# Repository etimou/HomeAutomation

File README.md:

# HomeAutomation

Installation on Raspberrypi
---------------------------

1. git clone https://github.com/etimou/HomeAutomation
2. sudo apt-get install python-serial lighttpd
3. sudo cp /etc/lighttpd/lighttpd.conf /etc/lighttpd/lighttpd.conf.sav
4. sudo nano /etc/lighttpd/lighttpd.conf
   replace "/var/www/html" by "/home/pi/HomeAutomation/software/raspberrypi/www"
   add "mod_cgi" in the server.modules section

   add
   cgi.assign                 = ( ".pl"  => "/usr/bin/perl",
                               ".cgi" => "/usr/bin/perl",
                               ".rb"  => "/usr/bin/ruby",
                               ".erb" => "/usr/bin/eruby",
                               ".py"  => "/usr/bin/python",
                               ".php" => "/usr/bin/php-cgi" )
  change port from 80 to 8181

5. sudo service lighttpd restart

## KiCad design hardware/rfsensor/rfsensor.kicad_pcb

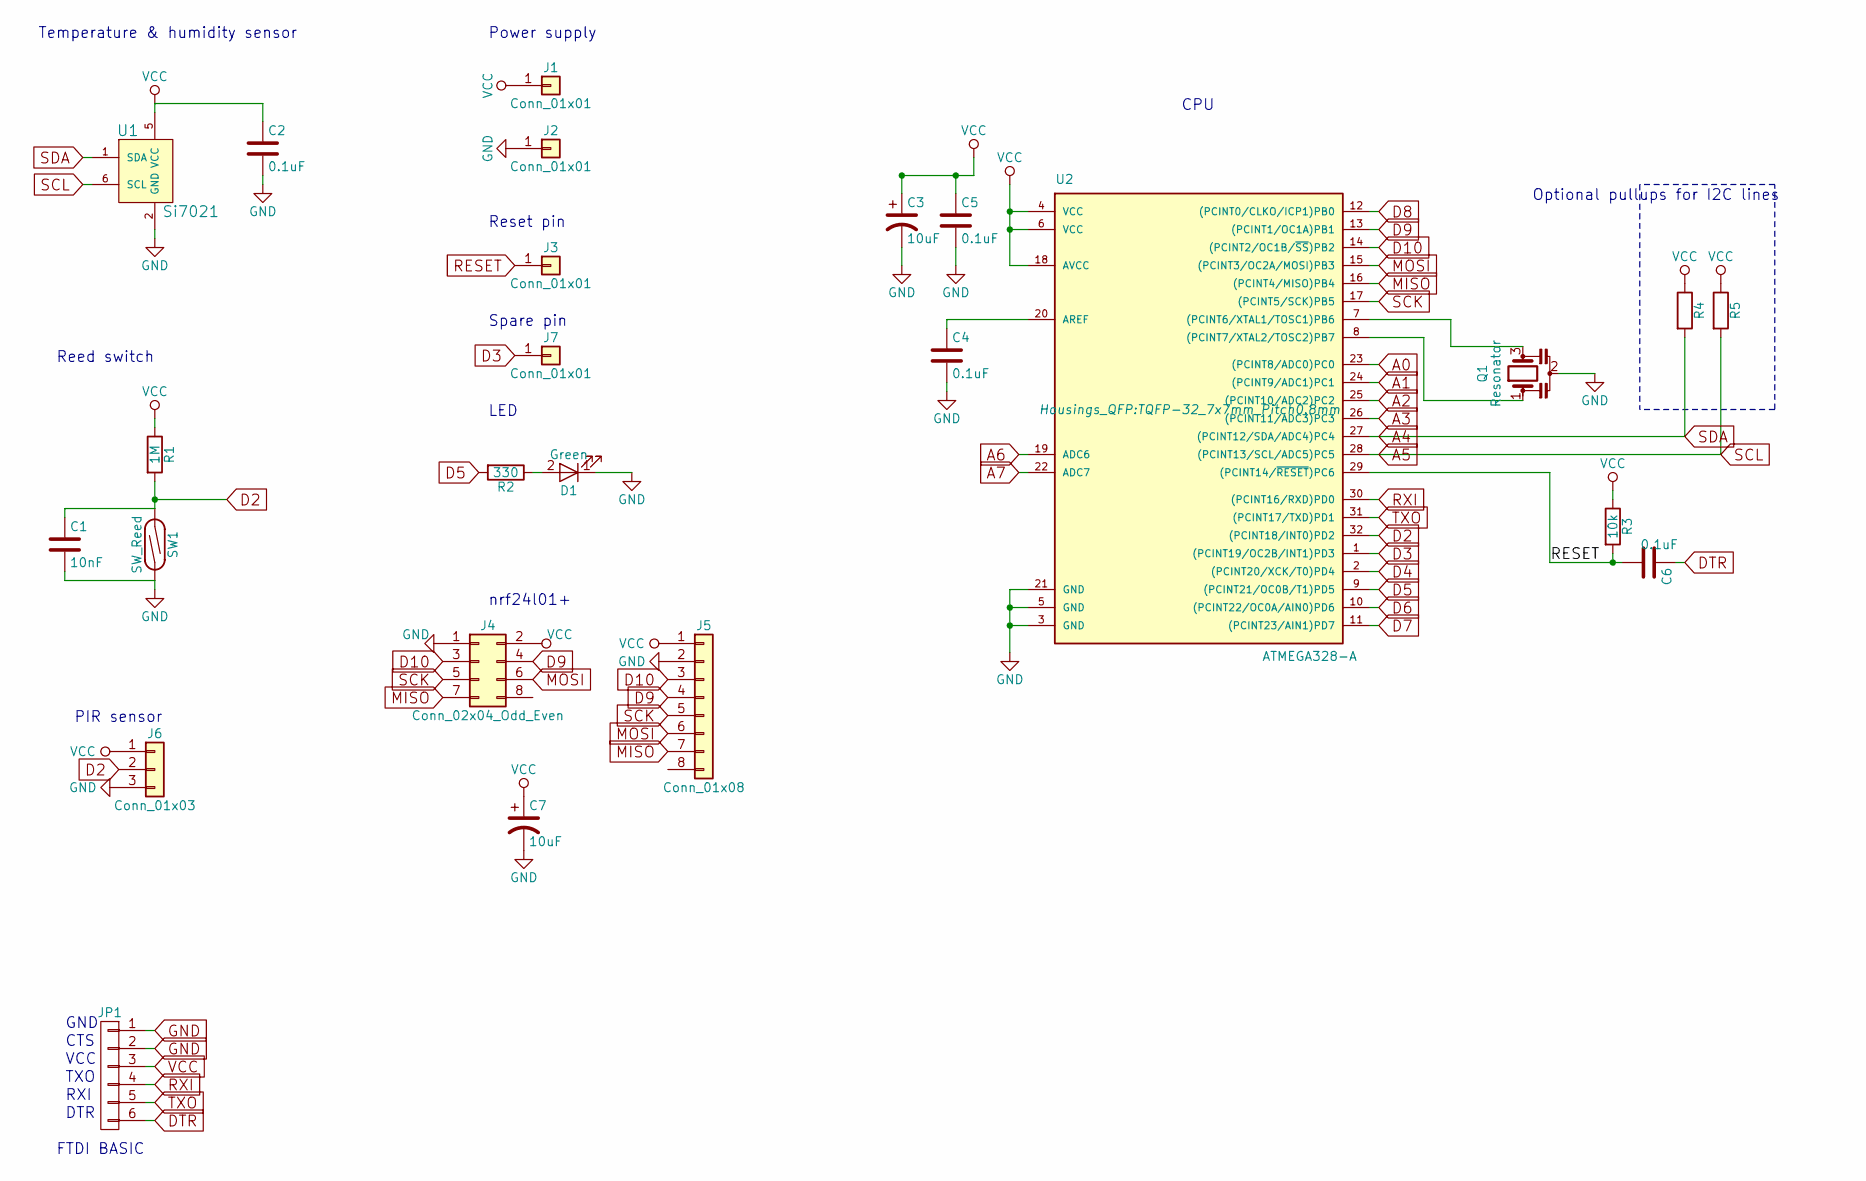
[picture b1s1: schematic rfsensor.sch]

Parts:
C1: 10nF; C_0603
C2, C4, C5, C6: 0.1uF; C_0603
C3, C7: 10uF; SMD-1206_Pol
D1: Green; LED_0603
J1, J2, J3, J7: Conn_01x01; Pin_Header_Straight_1x01_Pitch2.54mm
J4: Conn_02x04_Odd_Even; Pin_Header_Straight_2x04_Pitch2.54mm
J5: Conn_01x08; Pin_Header_Straight_1x08_Pitch1.27mm_SMD_Pin1Left
J6: Conn_01x03; Pin_Header_Straight_1x03_Pitch2.54mm
JP1: CONN_01X06; Pin_Header_Straight_1x06_Pitch2.54mm
Q1: Resonator; Resonator_smd
R1: 1M; R_0603
R2: 330; R_0603
R3: 10k; R_0603
R4, R5: R; R_0603
SW1: SW_Reed; reed
U1: Si7021; DFN-6-1EP_3x3mm_Pitch0.95mm
U2: ATMEGA328-A; TQFP-32_7x7mm_Pitch0.8mm

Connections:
A0: U2.23 ((PCINT8/ADC0)PC0)
A1: U2.24 ((PCINT9/ADC1)PC1)
A2: U2.25 ((PCINT10/ADC2)PC2)
A3: U2.26 ((PCINT11/ADC3)PC3)
A4: R4.2, U1.1 (SDA), U2.27 ((PCINT12/SDA/ADC4)PC4)
A5: R5.2, U1.6 (SCL), U2.28 ((PCINT13/SCL/ADC5)PC5)
A6: U2.19 (ADC6)
A7: U2.22 (ADC7)
D2: C1.1, J6.2, R1.2, SW1.1, U2.32 ((PCINT18/INT0)PD2)
D3: J7.1, U2.1 ((PCINT19/OC2B/INT1)PD3)
D4: U2.2 ((PCINT20/XCK/T0)PD4)
D5: R2.2, U2.9 ((PCINT21/OC0B/T1)PD5)
D6: U2.10 ((PCINT22/OC0A/AIN0)PD6)
D7: U2.11 ((PCINT23/AIN1)PD7)
D8: U2.12 ((PCINT0/CLKO/ICP1)PB0)
D9: J4.4, J5.4, U2.13 ((PCINT1/OC1A)PB1)
D10: J4.3, J5.3, U2.14 ((PCINT2/OC1B/~SS~)PB2)
DTR: C6.1, JP1.6
GND: C1.2, C2.2, C3.2, C4.2, C5.2, C7.2, D1.1 (K), J2.1, J4.1, J5.2, J6.3, JP1.1, JP1.2, Q1.2, SW1.2, U1.2 (GND), U2.3 (GND), U2.5 (GND), U2.21 (GND)
MISO: J4.7, J5.7, U2.16 ((PCINT4/MISO)PB4)
MOSI: J4.6, J5.6, U2.15 ((PCINT3/OC2A/MOSI)PB3)
unnamed: C4.1, U2.20 (AREF)
unnamed: D1.2 (A), R2.1
unnamed: Q1.1, U2.8 ((PCINT7/XTAL2/TOSC2)PB7)
unnamed: Q1.3, U2.7 ((PCINT6/XTAL1/TOSC1)PB6)
RESET: C6.2, J3.1, R3.2, U2.29 ((PCINT14/~RESET~)PC6)
RXI: JP1.4, U2.30 ((PCINT16/RXD)PD0)
SCK: J4.5, J5.5, U2.17 ((PCINT5/SCK)PB5)
TXO: JP1.5, U2.31 ((PCINT17/TXD)PD1)
VCC: C2.1, C3.1, C5.1, C7.1, J1.1, J4.2, J5.1, J6.1, JP1.3, R1.1, R3.1, R4.1, R5.1, U1.5 (VCC), U2.4 (VCC), U2.6 (VCC), U2.18 (AVCC)

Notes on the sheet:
Optional pullups for I2C lines
GND
CTS
VCC
TXO
RXI
DTR
FTDI BASIC
nrf24l01+
Power supply
Reset pin
Temperature & humidity sensor
Reed switch
CPU
LED
PIR sensor
Spare pin

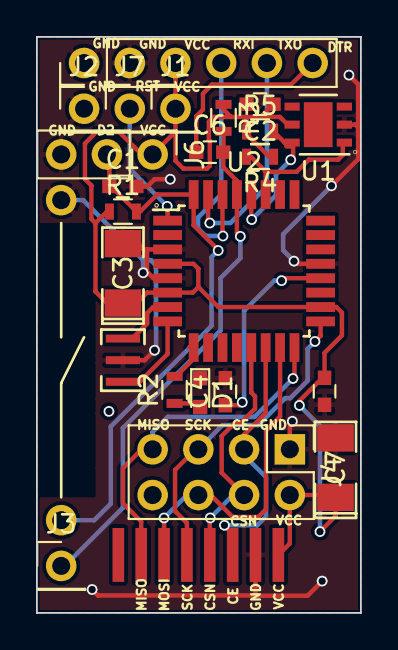
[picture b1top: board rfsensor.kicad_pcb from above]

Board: 2 copper layers, 18.0 x 32.0 mm, 25 parts (0 on the bottom side), 20 nets.

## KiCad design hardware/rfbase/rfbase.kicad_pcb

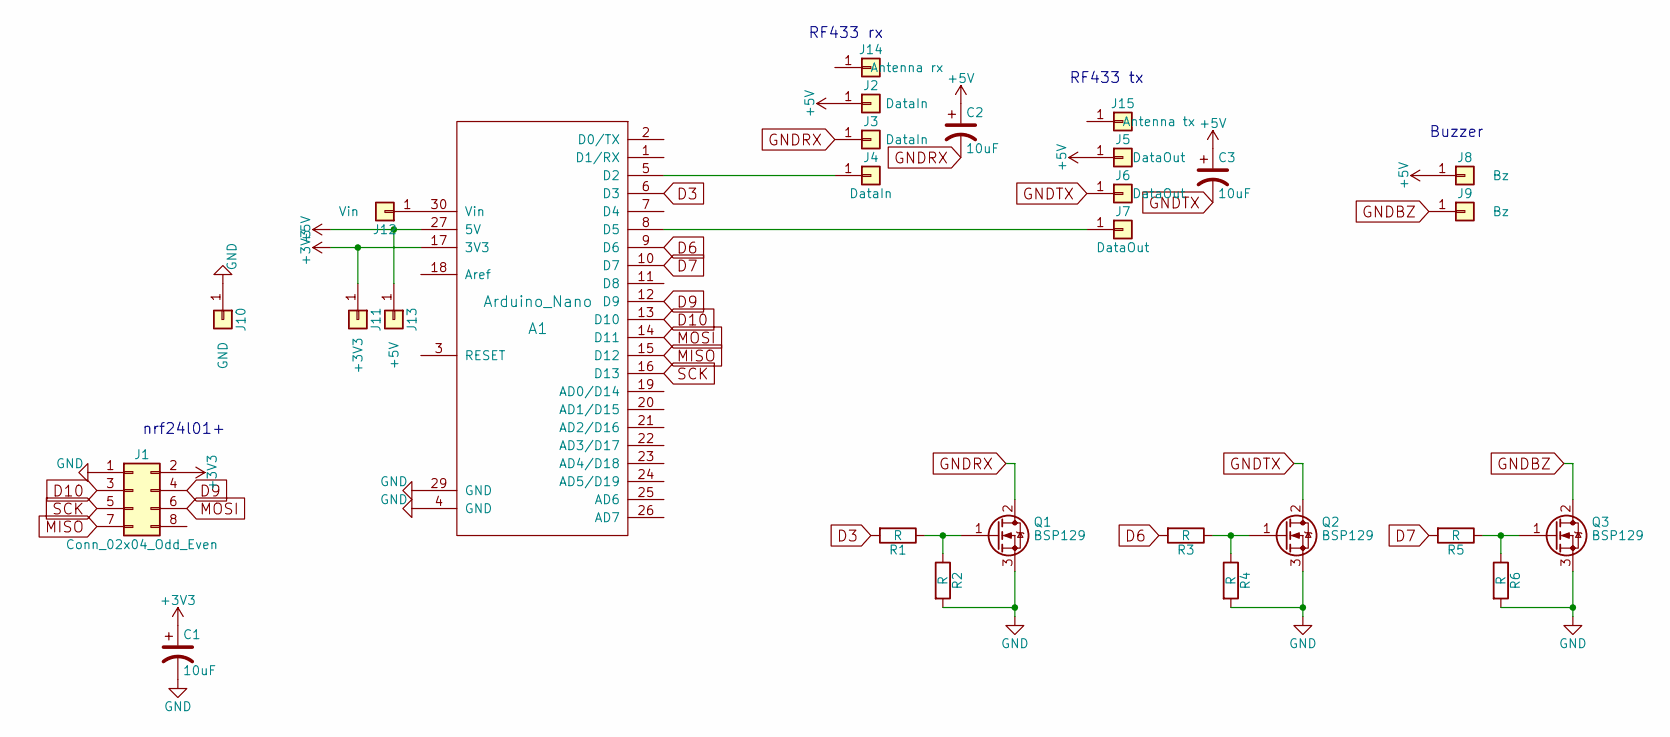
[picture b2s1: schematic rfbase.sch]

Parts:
A1: Arduino_Nano; arduino_nano
C1, C2, C3: 10uF; SMD-1206_Pol
J1: Conn_02x04_Odd_Even; Pin_Header_Straight_2x04_Pitch2.54mm
J2, J3, J4: DataIn; Pin_Header_Straight_1x01_Pitch2.54mm
J5, J6, J7: DataOut; Pin_Header_Straight_1x01_Pitch2.54mm
J8, J9: Bz; Pin_Header_Straight_1x01_Pitch2.54mm
J10: GND; Pin_Header_Straight_1x01_Pitch2.54mm
J11: +3V3; Pin_Header_Straight_1x01_Pitch2.54mm
J12: Vin; Pin_Header_Straight_1x01_Pitch2.54mm
J13: +5V; Pin_Header_Straight_1x01_Pitch2.54mm
J14: Antenna rx; Pin_Header_Straight_1x01_Pitch2.54mm
J15: Antenna tx; Pin_Header_Straight_1x01_Pitch2.54mm
Q1, Q2, Q3: BSP129; SOT-223-3Lead_TabPin2
R1, R2, R3, R4, R5, R6: R; R_0603

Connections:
+3V3: A1.17 (3V3), C1.1, J1.2, J11.1
+5V: A1.27 (5V), C2.1, C3.1, J2.1, J5.1, J8.1, J13.1
D3: A1.6 (D3), R1.2
D6: A1.9 (D6), R3.2
D7: A1.10 (D7), R5.2
D9: A1.12 (D9), J1.4
D10: A1.13 (D10), J1.3
GND: A1.4 (GND), A1.29 (GND), C1.2, J1.1, J10.1, Q1.3 (S), Q2.3 (S), Q3.3 (S), R2.2, R4.2, R6.2
GNDBZ: J9.1, Q3.2 (D)
GNDRX: C2.2, J3.1, Q1.2 (D)
GNDTX: C3.2, J6.1, Q2.2 (D)
MISO: A1.15 (D12), J1.7
MOSI: A1.14 (D11), J1.6
unnamed: A1.5 (D2), J4.1
unnamed: A1.8 (D5), J7.1
unnamed: A1.30 (Vin), J12.1
unnamed: Q1.1 (G), R1.1, R2.1
unnamed: Q2.1 (G), R3.1, R4.1
unnamed: Q3.1 (G), R5.1, R6.1
SCK: A1.16 (D13), J1.5

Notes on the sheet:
nrf24l01+
RF433 rx
RF433 tx
Buzzer

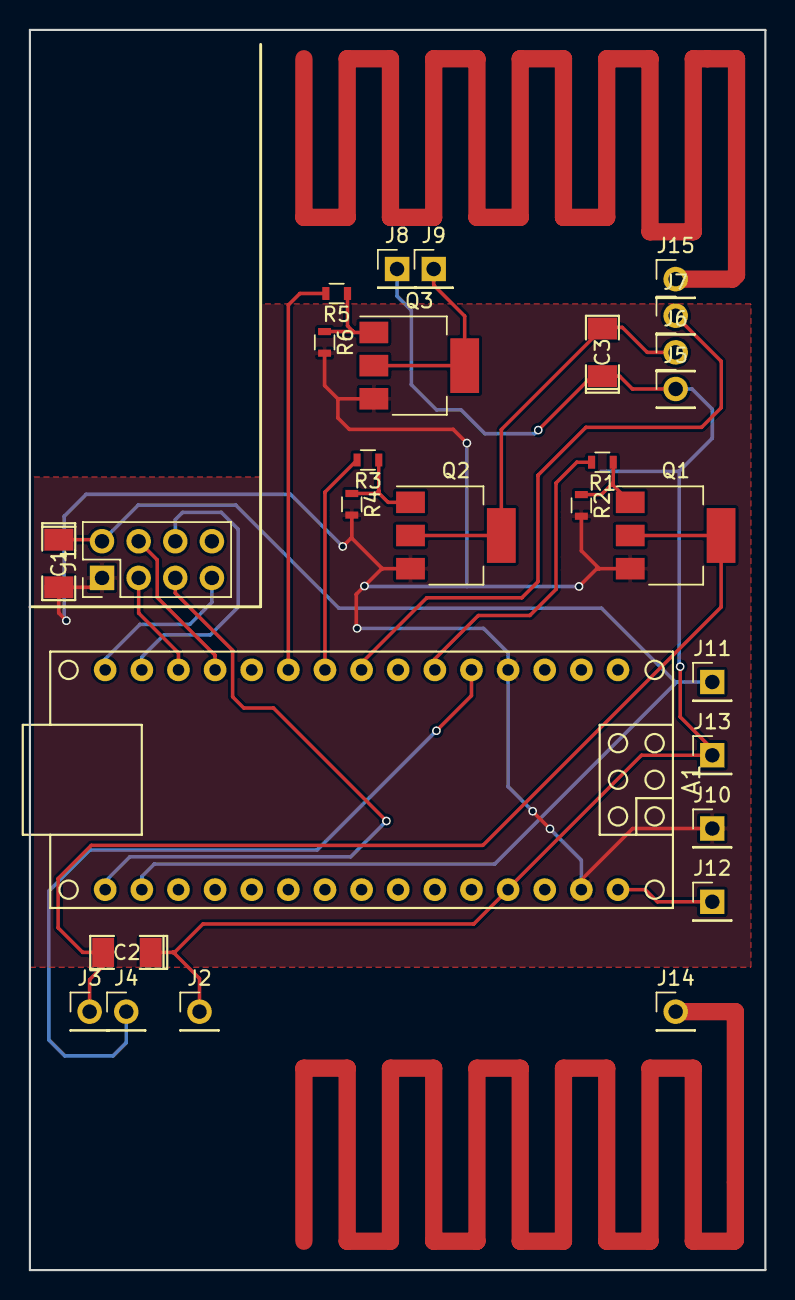
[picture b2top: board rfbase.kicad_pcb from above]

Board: 2 copper layers, 51.0 x 86.0 mm, 28 parts (0 on the bottom side), 20 nets.

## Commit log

2018-05-13 add files
2018-05-13 changes in file hierarchy
2018-10-08 add arduino files
2018-10-08 Net Base not sending OFF commnads to simple 433 devices
2018-10-08 add raspberrypi files
2018-10-08 arranged folders
2018-10-08 added sqlite database file
2018-10-08 changed sqlite database file location
2018-10-12 command alarm via web page
2018-10-13 gestion des sons pour activation/deactivation alarme
2018-10-19 modified actuators
2018-11-18 minor
2018-11-18 add scripts and sunwait program
2018-11-19 installation instructions
2018-11-20 use environment variable for the path
2018-11-20 hard path
2018-11-20 added one slash
2018-11-21 README
2018-11-25 changes in supervision.py
2018-12-15 logging stuff
2018-12-23 major update for supervision.py to manage TCP connections and be the only one accessing the serial port
2018-12-31 new generation NetBase.ino
2018-12-31 remove one comment
2019-01-01 new generation NetSensor and calibration3V3
2019-01-02 start to implement temperature
2019-01-04 management of temperature and include all data in CMD= in NetBase
2019-01-06 improved voltage measurement and calibration
2019-01-08 include option to calibrate aand set ID at startup
2019-01-09 adjusted V->% conversion
2019-01-11 minor update
2019-05-10 add keypad and updated domoticz backup
2019-09-15 add local PIR sensor
2020-04-03 align with current install
2020-11-14 tried to debug NetSensorPIR.ino
2021-01-16 upgrade to nodered
2021-01-16 cleaned up
2021-01-30 add keyboard
2023-04-29 suppression réception RF24 et 433
2023-05-27 Update NetBase.ino
    debouncing PIR input pin
2024-05-07 Update HomeAutomation.json
    no comment
